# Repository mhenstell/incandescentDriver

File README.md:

## Chandelier project

Four rings:
* 13 Elements
* 10 Elements
* 8 Elements
* 6 Elements
* Hanging bulb

Number of bulbs: (13 + 10 + 8 + 6) * 4 = 148 E12 globes ([PLT 219E24V5W](http://www.1000bulbs.com/product/61895/DEC-100150.html))

Number of bases: 148 E12 sockets ([SOCK-901556](http://www.1000bulbs.com/product/62223/SOCK-901556.html?ref=none))

Number of PCBs: (13 + 10 + 8 + 6) / 2 = 19 PCBs

Ring 1 (Outer) - 52 bulbs, 260 watts (11 amps)
Ring 2 - 40 bulbs, 200 watts (8.3 amps)
Ring 3 - 32 bulbs, 160 watts (7 amps)
Ring 4 (Inner) - 24 bulbs, 120 watts (5 amps)

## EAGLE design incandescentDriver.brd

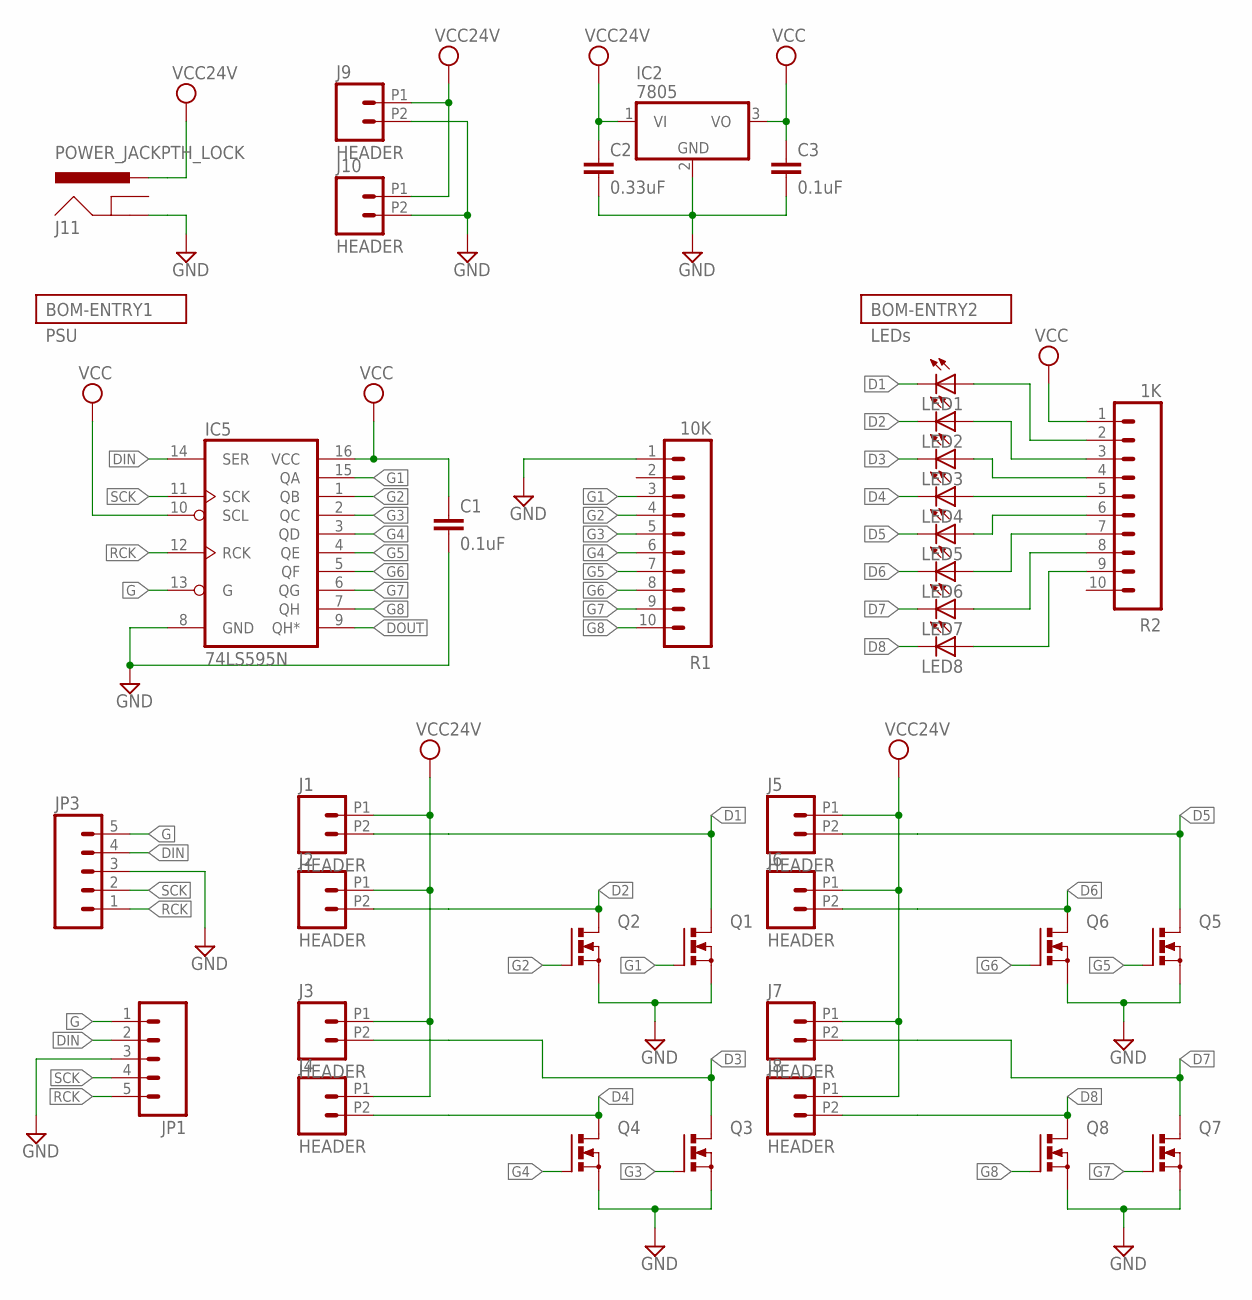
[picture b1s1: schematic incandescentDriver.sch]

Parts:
C1, C3: 0.1uF; CAP-PTH-SMALL; PARTNO SR295E104MAR
C2: 0.33uF; CAP-PTH-SMALL; PARTNO FK24X7R1H334K
IC2: 7805; TO220V; PARTNO NCP7805TG
IC5: 74LS595N; DIL16; PARTNO SN74HC164N
J1, J2, J3, J4, J5, J6, J7, J8, J9, J10: HEADER; 1X02-5.08-SCREWTERM; PARTNO OSTTC022162
J11: POWER_JACKPTH_LOCK; POWER_JACK_PTH_LOCK; PARTNO PJ-202A
JP1, JP3: M05LOCK; 1X05_LOCK; PARTNO M20-9960545
LED1, LED2, LED3, LED4, LED5, LED6, LED7, LED8: LED5MM
Q1, Q2, Q3, Q4, Q5, Q6, Q7, Q8: PMOSFET_NTO220BV; TO220BV; PARTNO FQP13N10L
R1: 10K; 1X10_LOCK; PARTNO L101S103LF
R2: 1K; 1X10_LOCK; PARTNO 4609X-101-102LF

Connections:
D1: J1.P2 (1), LED1.K (C), Q1.D
D2: J2.P2 (1), LED2.K (C), Q2.D
D3: J3.P2 (1), LED3.K (C), Q3.D
D4: J4.P2 (1), LED4.K (C), Q4.D
D5: J5.P2 (1), LED5.K (C), Q5.D
D6: J6.P2 (1), LED6.K (C), Q6.D
D7: J7.P2 (1), LED7.K (C), Q7.D
D8: J8.P2 (1), LED8.K (C), Q8.D
DIN: IC5.14 (SER), JP1.2, JP3.4
DOUT: IC5.9 (QH*)
G: IC5.13 (G), JP1.1, JP3.5
G1: IC5.15 (QA), Q1.G, R1.3
G2: IC5.1 (QB), Q2.G, R1.4
G3: IC5.2 (QC), Q3.G, R1.5
G4: IC5.3 (QD), Q4.G, R1.6
G5: IC5.4 (QE), Q5.G, R1.7
G6: IC5.5 (QF), Q6.G, R1.8
G7: IC5.6 (QG), Q7.G, R1.9
G8: IC5.7 (QH), Q8.G, R1.10
GND: C1.2, C2.2, C3.2, IC2.2 (GND), IC5.8 (GND), J9.P2 (1), J10.P2 (1), J11.GND, JP1.3, JP3.3, Q1.S, Q2.S, Q3.S, Q4.S, Q5.S, Q6.S, Q7.S, Q8.S, R1.1
unnamed: LED1.A, R2.2
unnamed: LED2.A, R2.3
unnamed: LED3.A, R2.4
unnamed: LED4.A, R2.5
unnamed: LED5.A, R2.6
unnamed: LED6.A, R2.7
unnamed: LED7.A, R2.8
unnamed: LED8.A, R2.9
RCK: IC5.12 (RCK), JP1.5, JP3.1
SCK: IC5.11 (SCK), JP1.4, JP3.2
VCC: C1.1, C3.1, IC2.3 (VO), IC5.10 (SCL), IC5.16 (VCC), R2.1
VCC24V: C2.1, IC2.1 (VI), J1.P1 (2), J2.P1 (2), J3.P1 (2), J4.P1 (2), J5.P1 (2), J6.P1 (2), J7.P1 (2), J8.P1 (2), J9.P1 (2), J10.P1 (2), J11.PWR

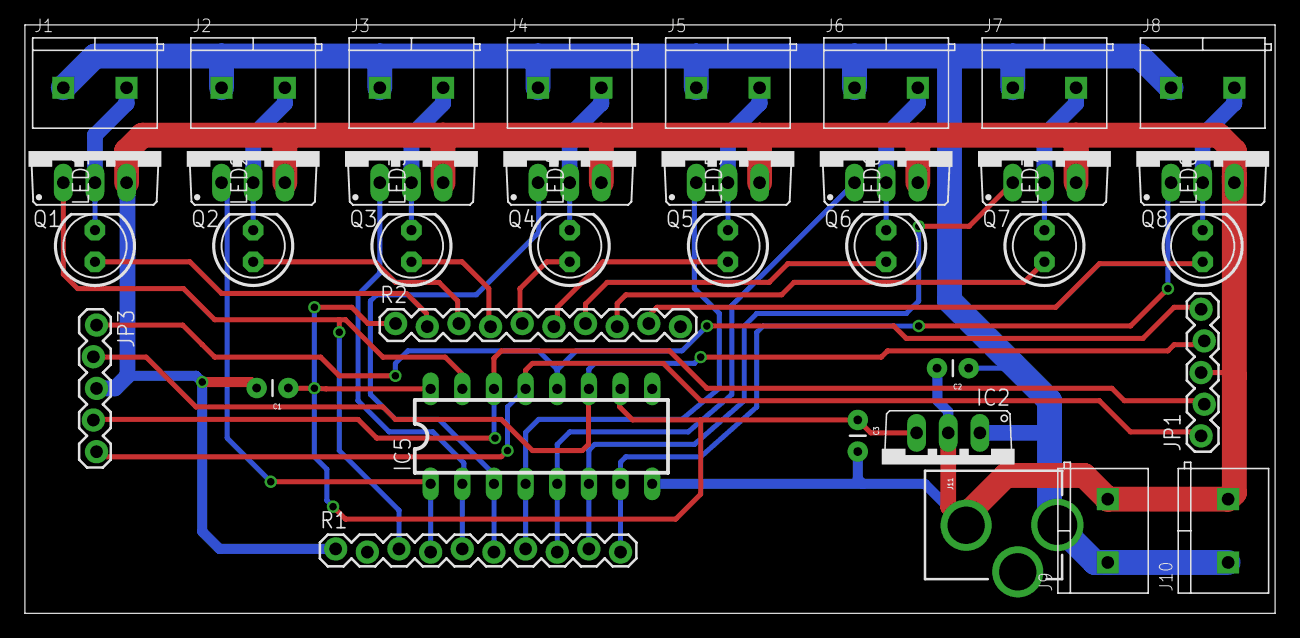
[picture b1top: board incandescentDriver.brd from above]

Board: 2 copper layers, 100.3 x 47.2 mm, 36 parts (0 on the bottom side), 31 nets.

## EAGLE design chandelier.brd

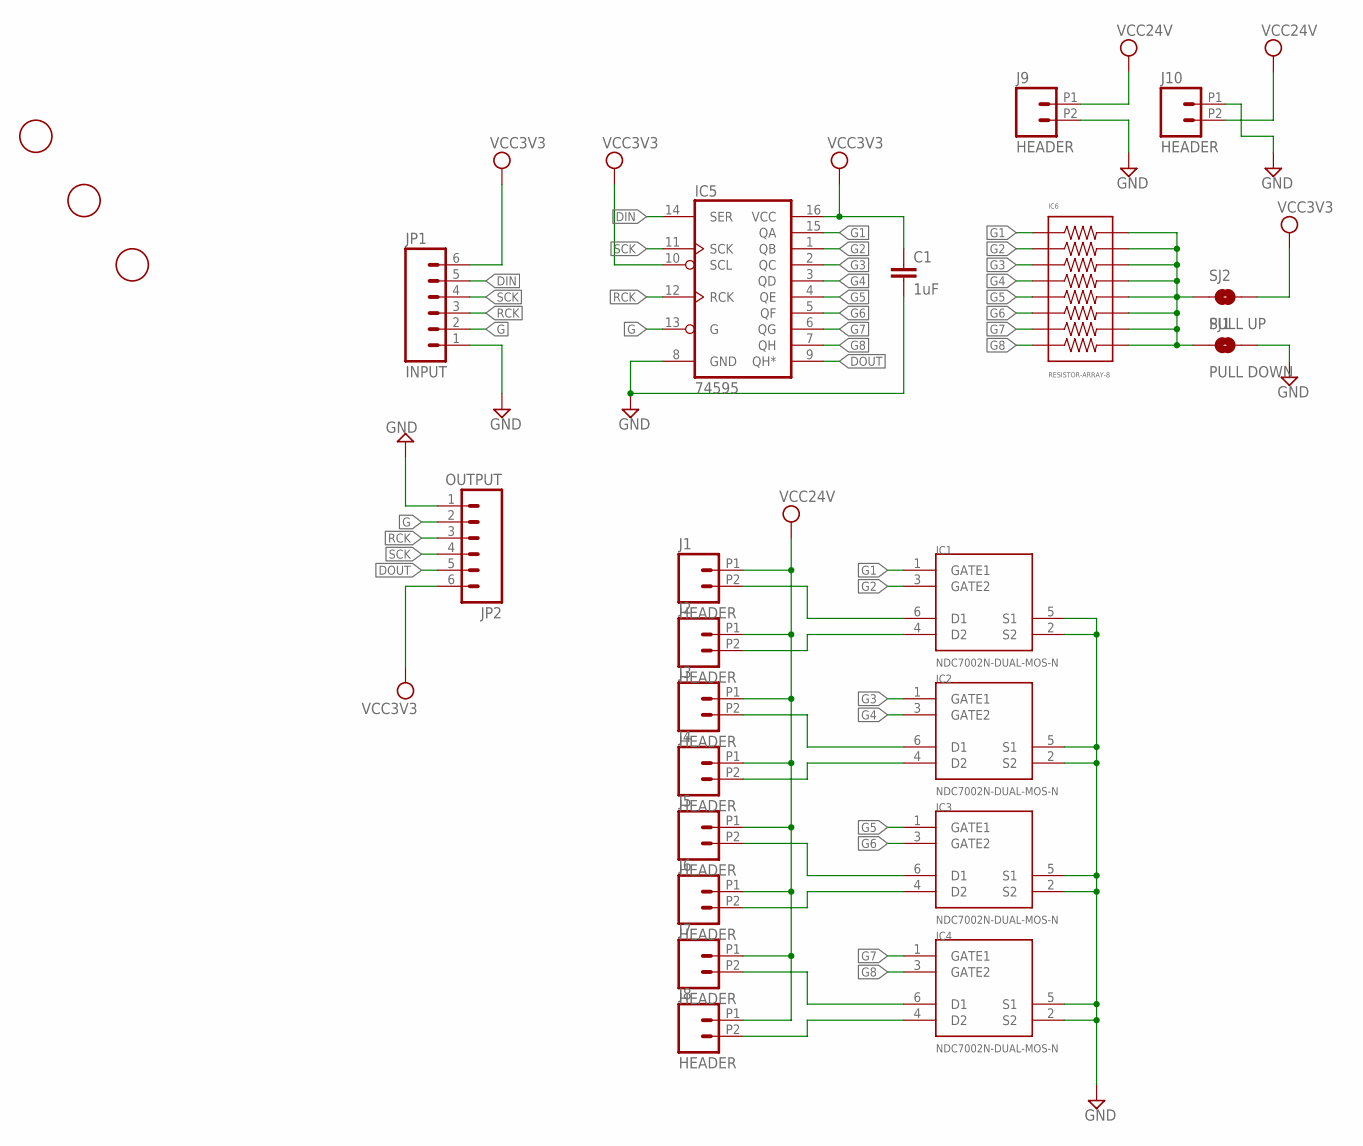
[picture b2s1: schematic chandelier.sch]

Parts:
C1: 1uF; 0805; PARTNO CL21B105KOFNNNE
IC1, IC2, IC3, IC4: NDC7002N-DUAL-MOS-N; SSOT6; PARTNO NDC7002N
IC5: 74595; TSSOP16; PARTNO 74VHC595MTCX
IC6: RESISTOR-ARRAY-8; CAY16-103J8; PARTNO CAY16-103J8LF
J1, J2, J3, J4, J5, J6, J7, J8, J9, J10: HEADER; 1X02-5.08-SCREWTERM
JP1: INPUT; 1X06-SIP_LOCK
JP2: OUTPUT; 1X06-SIP_LOCK
SJ1: PULL DOWN; SJ_2S-TRACE
SJ2: PULL UP; SJ_2S-NO
U$1, U$4, U$5: FIDUCIAL; FIDUCIAL_1MM

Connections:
DIN: IC5.14 (SER), JP1.5
DOUT: IC5.9 (QH*), JP2.5
G: IC5.13 (G), JP1.2, JP2.2
G1: IC1.1 (GATE1), IC5.15 (QA), IC6.2
G2: IC1.3 (GATE2), IC5.1 (QB), IC6.4
G3: IC2.1 (GATE1), IC5.2 (QC), IC6.6
G4: IC2.3 (GATE2), IC5.3 (QD), IC6.8
G5: IC3.1 (GATE1), IC5.4 (QE), IC6.10
G6: IC3.3 (GATE2), IC5.5 (QF), IC6.12
G7: IC4.1 (GATE1), IC5.6 (QG), IC6.14
G8: IC4.3 (GATE2), IC5.7 (QH), IC6.16
GND: C1.2, IC1.2 (S2), IC1.5 (S1), IC2.2 (S2), IC2.5 (S1), IC3.2 (S2), IC3.5 (S1), IC4.2 (S2), IC4.5 (S1), IC5.8 (GND), J9.P2 (1), J10.P1 (2), JP1.1, JP2.1, SJ1.2
unnamed: IC1.6 (D1), J1.P2 (1)
unnamed: IC1.4 (D2), J2.P2 (1)
unnamed: IC2.6 (D1), J3.P2 (1)
unnamed: IC2.4 (D2), J4.P2 (1)
unnamed: IC3.6 (D1), J5.P2 (1)
unnamed: IC3.4 (D2), J6.P2 (1)
unnamed: IC4.6 (D1), J7.P2 (1)
unnamed: IC4.4 (D2), J8.P2 (1)
unnamed: IC6.1, IC6.3, IC6.5, IC6.7, IC6.9, IC6.11, IC6.13, IC6.15, SJ1.1, SJ2.1
RCK: IC5.12 (RCK), JP1.3, JP2.3
SCK: IC5.11 (SCK), JP1.4, JP2.4
VCC3V3: C1.1, IC5.10 (SCL), IC5.16 (VCC), JP1.6, JP2.6, SJ2.2
VCC24V: J1.P1 (2), J2.P1 (2), J3.P1 (2), J4.P1 (2), J5.P1 (2), J6.P1 (2), J7.P1 (2), J8.P1 (2), J9.P1 (2), J10.P2 (1)

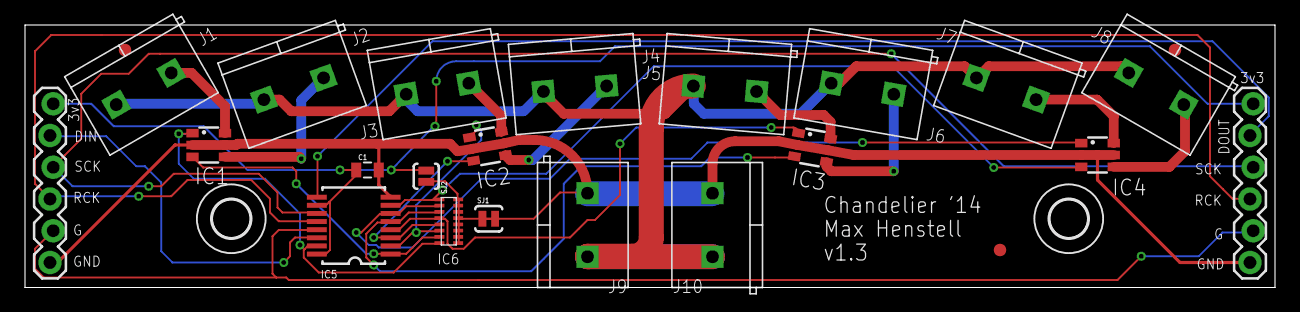
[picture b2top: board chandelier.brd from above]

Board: 2 copper layers, 100.0 x 21.0 mm, 26 parts (0 on the bottom side), 25 nets.

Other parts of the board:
U$2, U$3: HOLE-3

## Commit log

2014-04-14 init
2014-04-14 adding gitignore
2014-04-15 updating gitignore for eagle files
2014-04-15 adding mosfet driver
2014-04-29 adding uncommitted things
2014-05-08 added bom
2014-05-09 added num of elements
2014-05-11 adding dxfs
2014-05-11 added radii
2014-05-12 wood and braces
2014-05-14 adding readme
2014-05-15 making simulator 2d
2014-05-15 updating sim
2014-05-18 added transmitter with some routines, fixes to the simulator
2014-05-19 added small braces
2014-05-19 added center bulb
2014-05-19 adding arduino firmware and python host
2014-05-22 updating readme
2014-05-22 updated board to fix footprint issue
2014-05-22 fixed braces angles? and put all in one file
2014-05-22 test firmware/host
2014-05-25 working for ring 4
2014-05-30 adding makefile
2014-05-30 fixed trace issues for 1.3
2014-06-06 adding new incandescent board
2014-06-06 working on BOM
2014-06-23 cleaning up older chandelier stuff

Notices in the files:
parts and their libraries:
SparkFun-DigitalIC: Licensing: CC v3.0 Share-Alike You are welcome to use this library for commercial purposes.
bom: Copyright (C) 2010, Bob Starr
